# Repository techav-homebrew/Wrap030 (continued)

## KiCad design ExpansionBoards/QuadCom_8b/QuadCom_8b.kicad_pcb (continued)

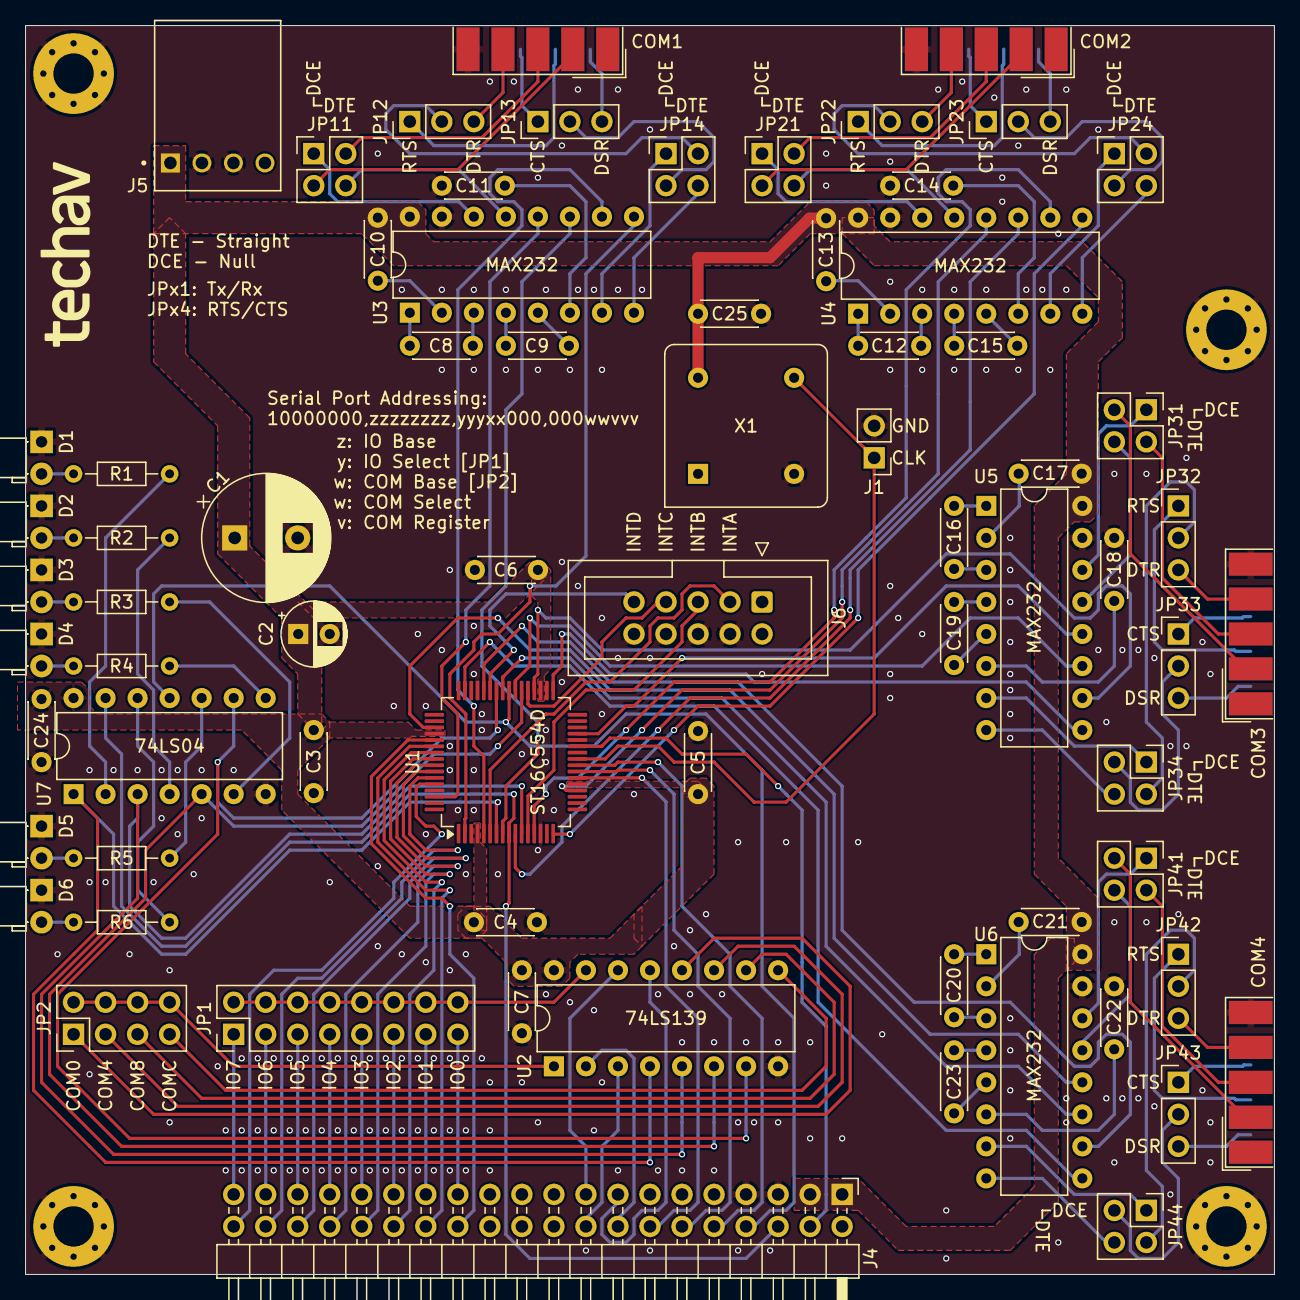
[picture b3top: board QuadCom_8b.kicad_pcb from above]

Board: 2 copper layers, 99.1 x 99.1 mm, 75 parts (0 on the bottom side), 143 nets.

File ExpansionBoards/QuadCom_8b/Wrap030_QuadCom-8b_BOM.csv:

"Reference","Value","Datasheet","Footprint","Qty","DNP","Mouser"
"C1","100uF","~","Capacitor_THT:CP_Radial_D10.0mm_P5.00mm","1","",""
"C2","10uF","~","Capacitor_THT:CP_Radial_D5.0mm_P2.50mm","1","",""
"C3,C4,C5,C6,C7,C24","100nF","~","Capacitor_THT:C_Disc_D4.3mm_W1.9mm_P5.00mm","6","",""
"C8,C9,C10,C11,C12,C13,C14,C15,C16,C17,C18,C19,C20,C21,C22,C23","1uF","~","Capacitor_THT:C_Disc_D4.3mm_W1.9mm_P5.00mm","16","",""
"COM1,COM2,COM3,COM4","DE9_Plug","~","Connector_Dsub:DSUB-9_Male_EdgeMount_P2.77mm","4","",""
"D1,D2,D3,D4,D5,D6","LED","~","LED_THT:LED_D3.0mm_Horizontal_O1.27mm_Z2.0mm","6","",""
"J4","Conn_02x20_Odd_Even","~","Connector_PinHeader_2.54mm:PinHeader_2x20_P2.54mm_Horizontal","1","",""
"J5","4-171826-4","","QuadCom_8b:TE_4-171826-4","1","",""
"J6","Conn_02x05_Odd_Even","~","Connector_IDC:IDC-Header_2x05_P2.54mm_Vertical","1","",""
"JP1","Conn_02x08_Odd_Even","~","Connector_PinHeader_2.54mm:PinHeader_2x08_P2.54mm_Vertical","1","",""
"JP2","Conn_02x04_Odd_Even","~","Connector_PinHeader_2.54mm:PinHeader_2x04_P2.54mm_Vertical","1","",""
"JP11,JP14,JP21,JP24,JP31,JP34,JP41,JP44","Conn_02x02_Odd_Even","~","Connector_PinHeader_2.54mm:PinHeader_2x02_P2.54mm_Vertical","8","",""
"JP12,JP13,JP22,JP23,JP32,JP33,JP42,JP43","Conn_01x03","~","Connector_PinHeader_2.54mm:PinHeader_1x03_P2.54mm_Vertical","8","",""
"R1,R2,R3,R4,R5,R6","4k7","~","Resistor_THT:R_Axial_DIN0204_L3.6mm_D1.6mm_P7.62mm_Horizontal","6","",""
"U1","ST16C554D","https://www.mouser.com/datasheet/2/146/ST16C554_ST16C554D_ST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","Package_QFP:LQFP-64_10x10mm_P0.5mm","1","","701-ST16C554DIQ64-F"
"U2","74LS139","http://www.ti.com/lit/ds/symlink/sn74ls139a.pdf","Package_DIP:DIP-16_W7.62mm","1","",""
"U3,U4,U5,U6","MAX232","http://www.ti.com/lit/ds/symlink/max232.pdf","Package_DIP:DIP-16_W7.62mm","4","",""
"U7","74LS04","http://www.ti.com/lit/gpn/sn74LS04","Package_DIP:DIP-14_W7.62mm","1","",""

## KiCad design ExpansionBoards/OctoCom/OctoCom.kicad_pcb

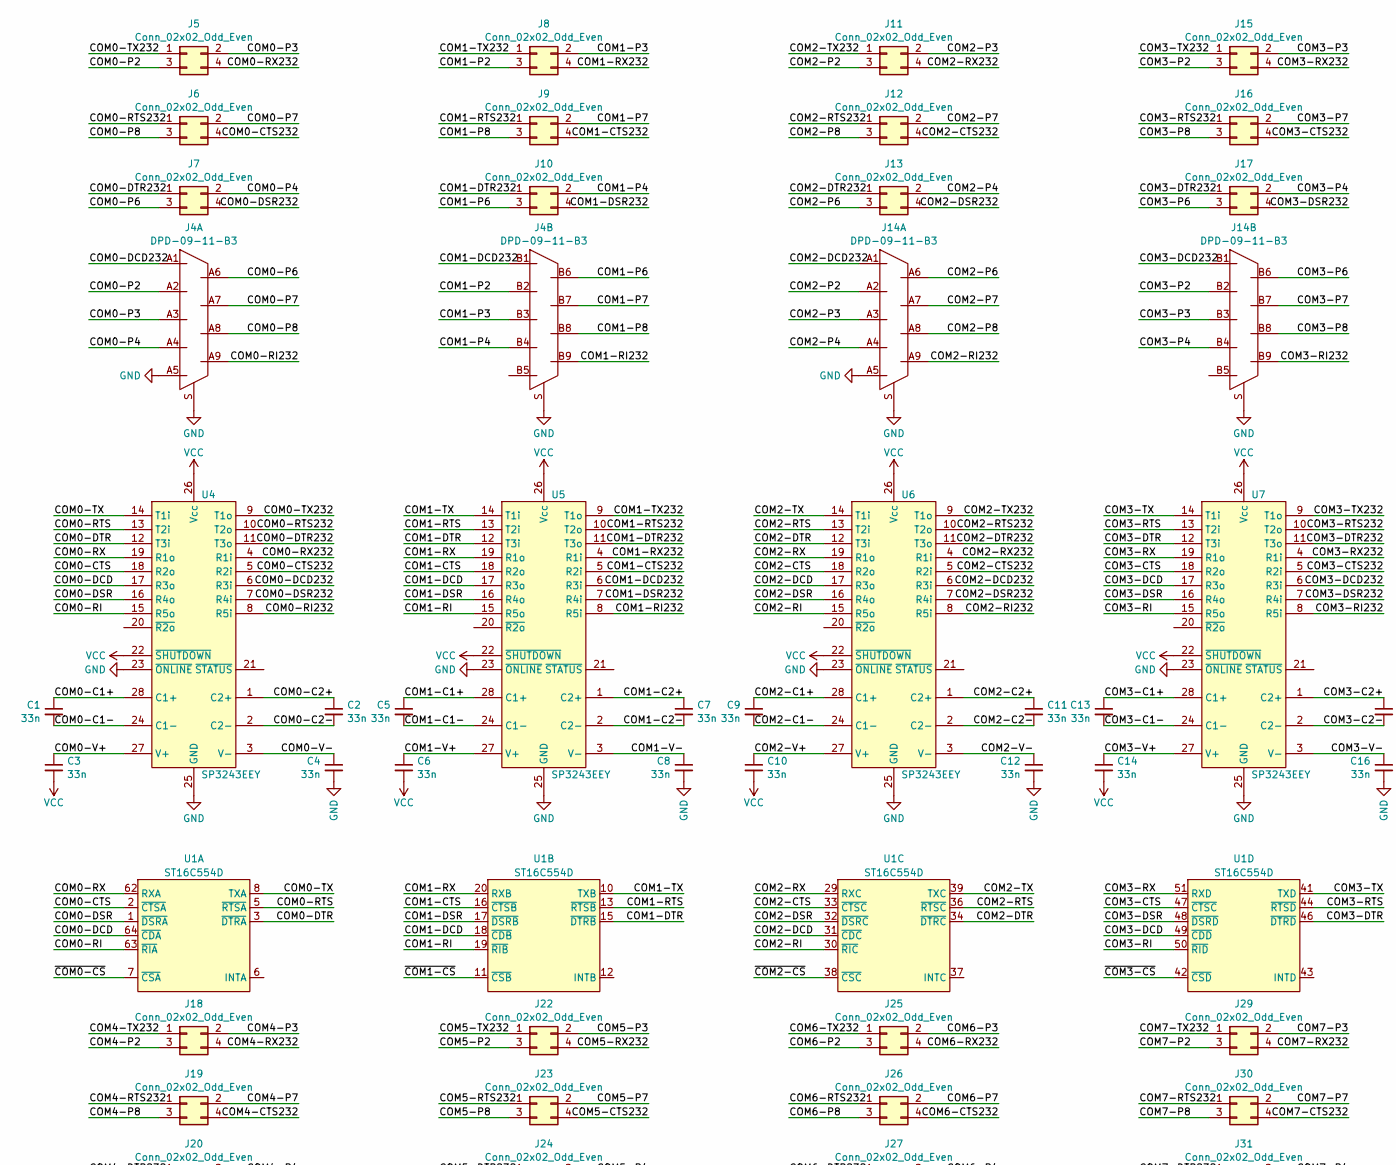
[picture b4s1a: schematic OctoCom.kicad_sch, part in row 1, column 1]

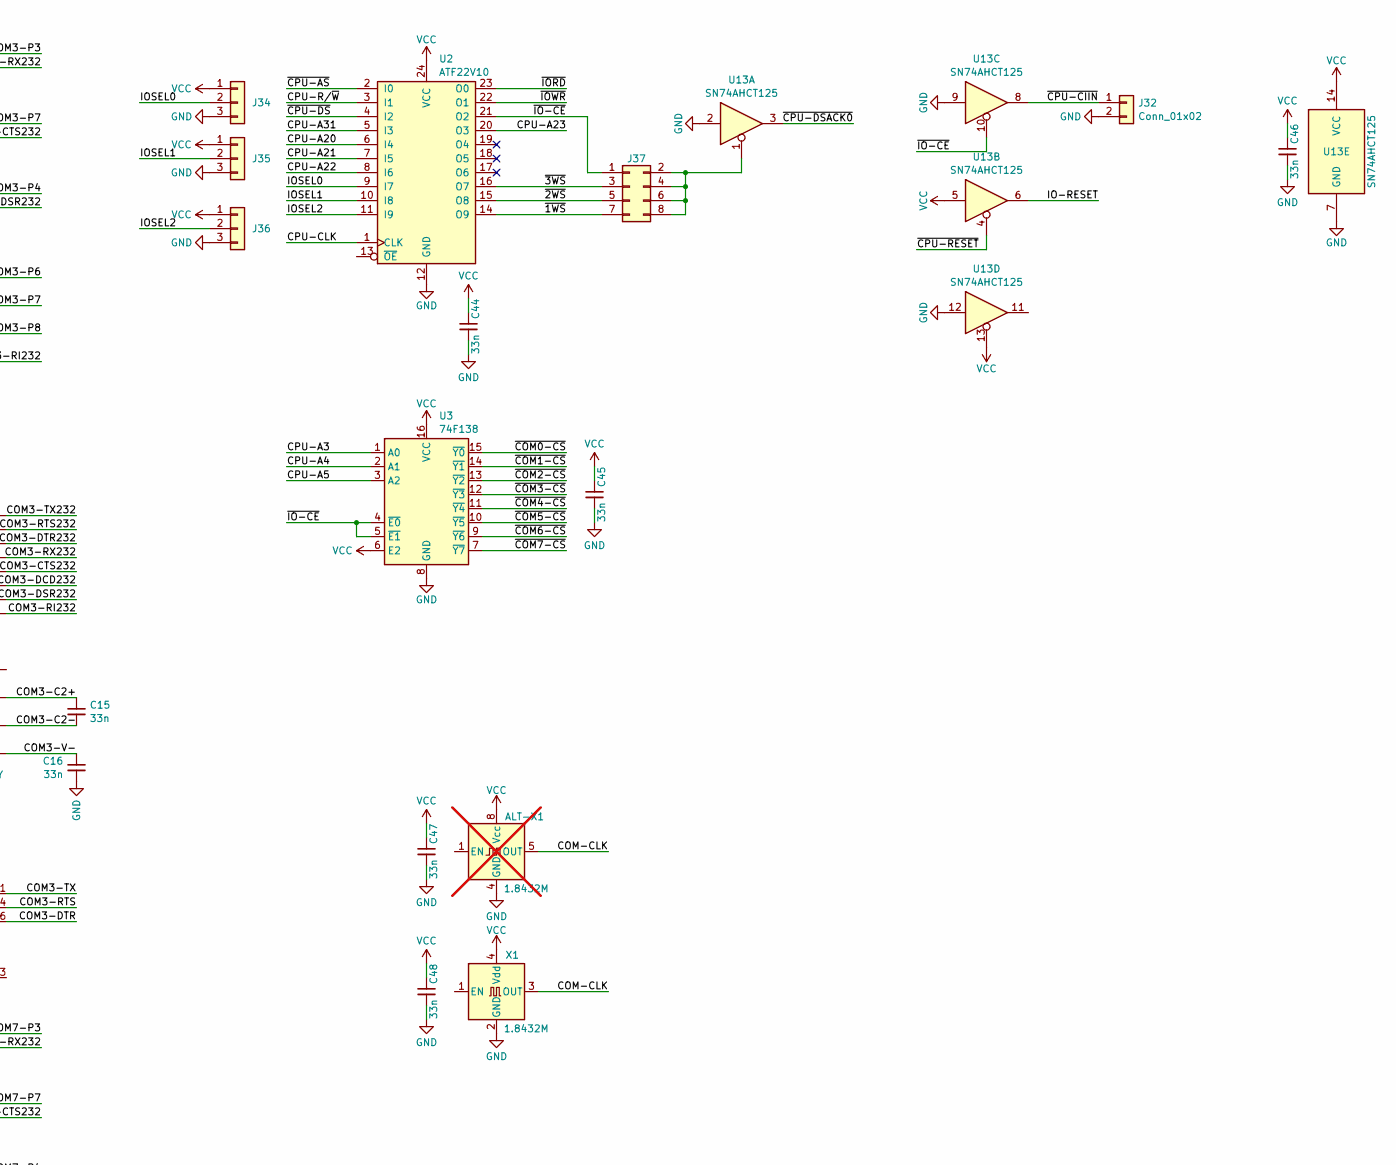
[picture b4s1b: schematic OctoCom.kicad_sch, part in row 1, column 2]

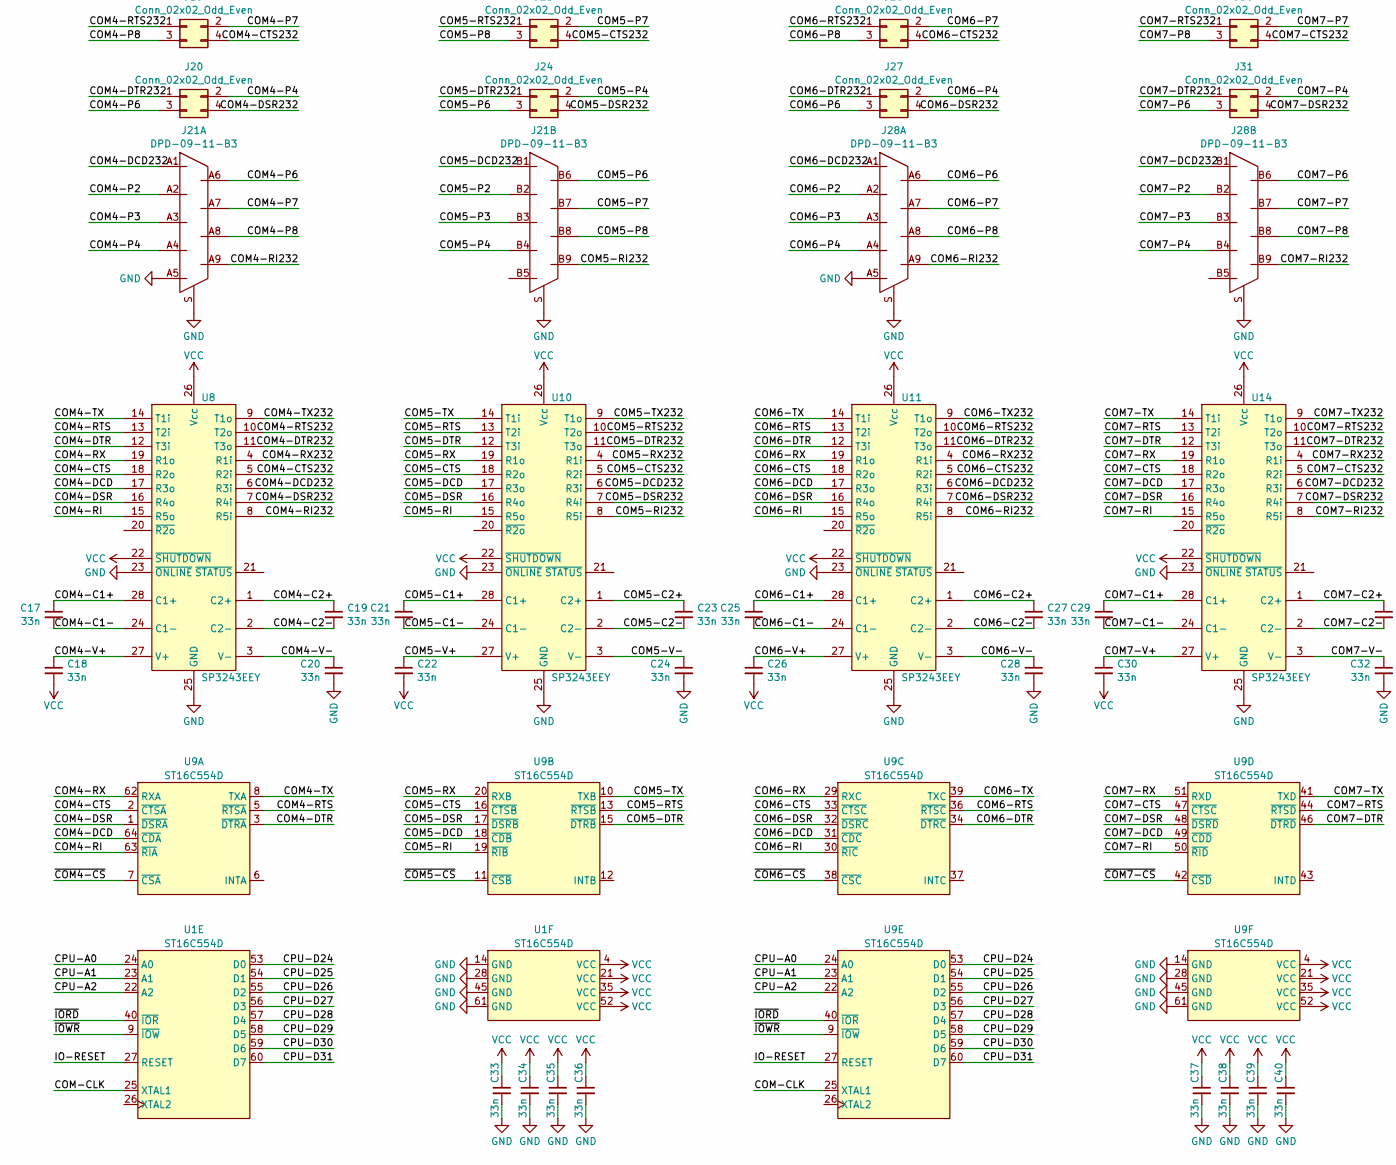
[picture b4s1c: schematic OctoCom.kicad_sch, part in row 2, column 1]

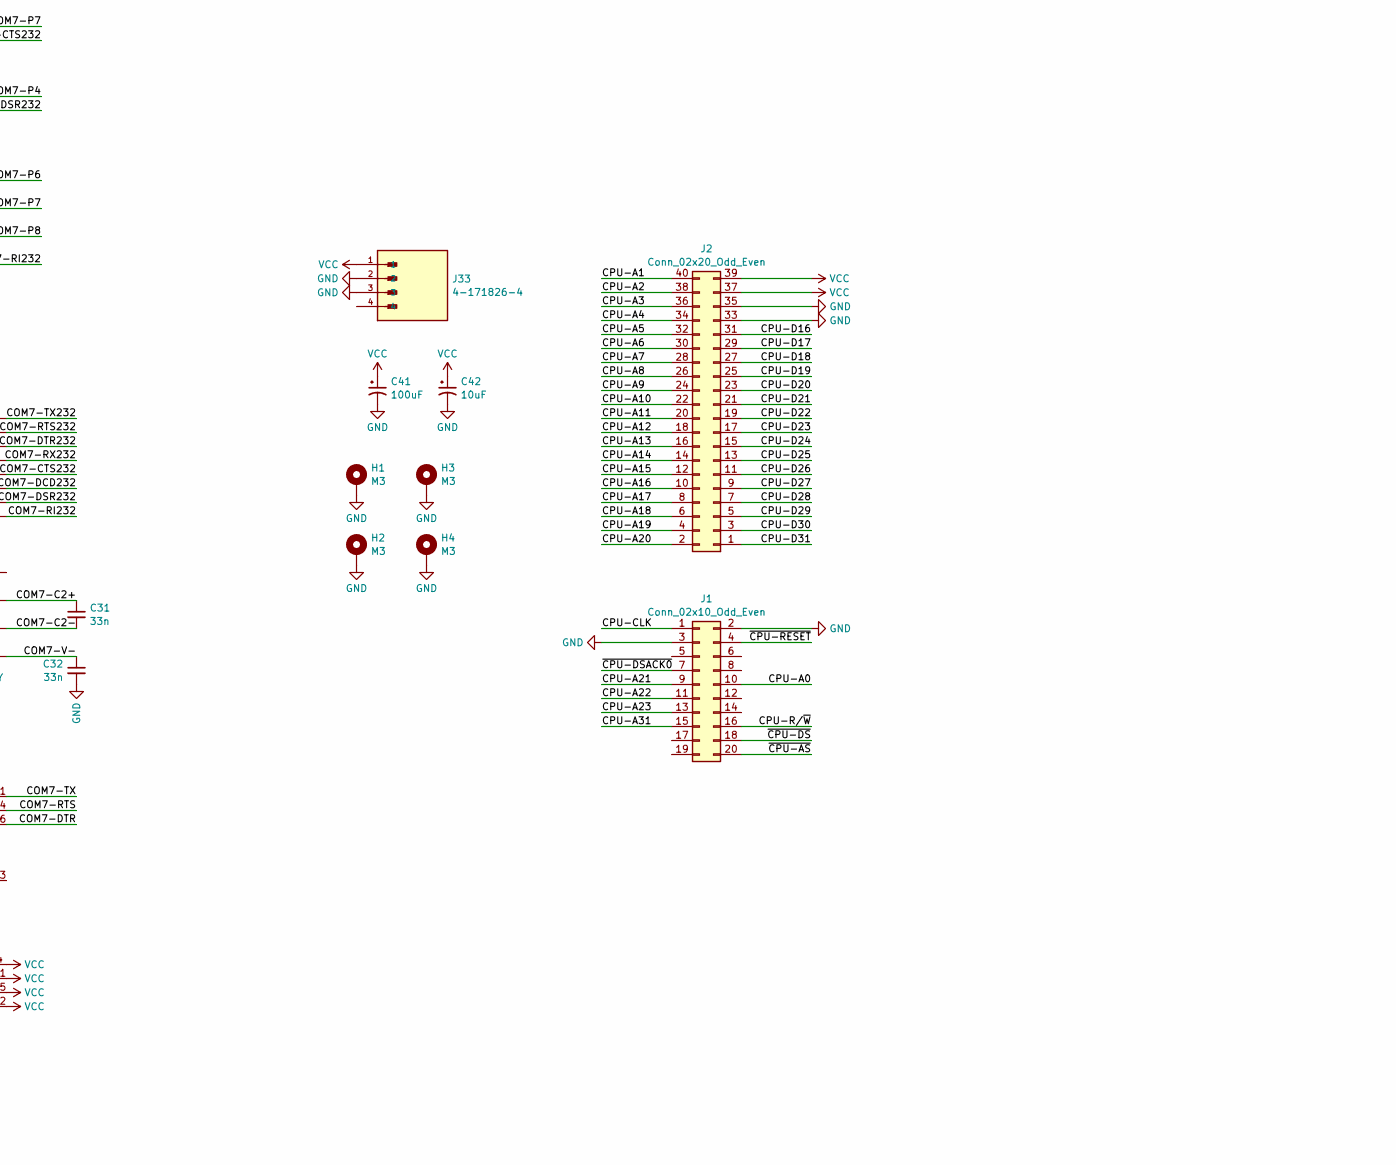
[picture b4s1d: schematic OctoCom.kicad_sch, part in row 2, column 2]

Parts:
ALT-X1: 1.8432M; Oscillator_DIP-8; Mouser 520-TCH184-X; not fitted
C1, C2, C3, C4, C5, C6, C7, C8, C9, C10, C11, C12, C13, C14, C15, C16, C17, C18, C19, C20, C21, C22, C23, C24, C25, C26, C27, C28, C29, C30, C31, C32, C33, C34, C35, C36, C37, C38, C39, C40, C44, C45, C46, C47, C48: 33n; C_0805_2012Metric_Pad1.18x1.45mm_HandSolder; Mouser 791-0805B333K160CT
C41: 100uF; CP_Radial_D10.0mm_P5.00mm
C42: 10uF; CP_Radial_D5.0mm_P2.50mm
H1, H2, H3, H4: M3; MountingHole_3.2mm_M3_Pad_Via
J1: Conn_02x10_Odd_Even; PinHeader_2x10_P2.54mm_Horizontal
J2: Conn_02x20_Odd_Even; PinHeader_2x20_P2.54mm_Horizontal
J4, J14, J21, J28: DPD-09-11-B3; Mouser 737-DPD-09-11-B3
J5, J6, J7, J8, J9, J10, J11, J12, J13, J15, J16, J17, J18, J19, J20, J22, J23, J24, J25, J26, J27, J29, J30, J31: Conn_02x02_Odd_Even; PinHeader_2x02_P2.54mm_Vertical
J32: Conn_01x02; PinHeader_1x02_P2.54mm_Vertical
J33: 4-171826-4; TE_4-171826-4
J34, J35, J36: Conn_01x03; PinHeader_1x03_P2.54mm_Vertical
J37: Conn_02x04_Odd_Even; PinHeader_2x04_P2.54mm_Vertical
U1, U9: ST16C554D; LQFP-64_10x10mm_P0.5mm; Mouser 701-ST16C554DIQ64-F
U2: ATF22V10; DIP-24_W7.62mm; Mouser 556-AF22V10C7PX
U3: 74F138; DIP-16_W7.62mm; Mouser 595-SN74F138N
U4, U5, U6, U7, U8, U10, U11, U14: SP3243EEY; TSSOP-28_4.4x9.7mm_P0.65mm; Mouser 701-SP3243EEY-L
U13: SN74AHCT125; SO-14_3.9x8.65mm_P1.27mm; Mouser 595-SN74AHCT125DR
X1: 1.8432M; Oscillator_SMD_Abracon_ASV-4Pin_7.0x5.1mm; JLC C386895

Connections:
/COM0-C1+: C1.1, U4.28 (C1+)
/COM0-C1-: C1.2, U4.24 (C1-)
/COM0-C2+: C2.1, U4.1 (C2+)
/COM0-C2-: C2.2, U4.2 (C2-)
/COM0-CTS: U1.2 (~CTSA), U4.18 (R2o)
/COM0-CTS232: J6.4, U4.5 (R2i)
/COM0-DCD: U1.64 (~CDA), U4.17 (R3o)
/COM0-DCD232: J4.A1, U4.6 (R3i)
/COM0-DSR: U1.1 (~DSRA), U4.16 (R4o)
/COM0-DSR232: J7.4, U4.7 (R4i)
/COM0-DTR: U1.3 (~DTRA), U4.12 (T3i)
/COM0-DTR232: J7.1, U4.11 (T3o)
/COM0-P2: J4.A2, J5.3
/COM0-P3: J4.A3, J5.2
/COM0-P4: J4.A4, J7.2
/COM0-P6: J4.A6, J7.3
/COM0-P7: J4.A7, J6.2
/COM0-P8: J4.A8, J6.3
/COM0-RI: U1.63 (~RIA), U4.15 (R5o)
/COM0-RI232: J4.A9, U4.8 (R5i)
/COM0-RTS: U1.5 (~RTSA), U4.13 (T2i)
/COM0-RTS232: J6.1, U4.10 (T2o)
/COM0-RX: U1.62 (RXA), U4.19 (R1o)
/COM0-RX232: J5.4, U4.4 (R1i)
/COM0-TX: U1.8 (TXA), U4.14 (T1i)
/COM0-TX232: J5.1, U4.9 (T1o)
/COM0-V+: C3.1, U4.27 (V+)
/COM0-V-: C4.1, U4.3 (V-)
/COM1-C1+: C5.1, U5.28 (C1+)
/COM1-C1-: C5.2, U5.24 (C1-)
/COM1-C2+: C7.1, U5.1 (C2+)
/COM1-C2-: C7.2, U5.2 (C2-)
/COM1-CTS: U1.16 (~CTSB), U5.18 (R2o)
/COM1-CTS232: J9.4, U5.5 (R2i)
/COM1-DCD: U1.18 (~CDB), U5.17 (R3o)
/COM1-DCD232: J4.B1, U5.6 (R3i)
/COM1-DSR: U1.17 (~DSRB), U5.16 (R4o)
/COM1-DSR232: J10.4, U5.7 (R4i)
/COM1-DTR: U1.15 (~DTRB), U5.12 (T3i)
/COM1-DTR232: J10.1, U5.11 (T3o)
/COM1-P2: J4.B2, J8.3
/COM1-P3: J4.B3, J8.2
/COM1-P4: J4.B4, J10.2
/COM1-P6: J4.B6, J10.3
/COM1-P7: J4.B7, J9.2
/COM1-P8: J4.B8, J9.3
/COM1-RI: U1.19 (~RIB), U5.15 (R5o)
/COM1-RI232: J4.B9, U5.8 (R5i)
/COM1-RTS: U1.13 (~RTSB), U5.13 (T2i)
/COM1-RTS232: J9.1, U5.10 (T2o)
/COM1-RX: U1.20 (RXB), U5.19 (R1o)
/COM1-RX232: J8.4, U5.4 (R1i)
/COM1-TX: U1.10 (TXB), U5.14 (T1i)
/COM1-TX232: J8.1, U5.9 (T1o)
/COM1-V+: C6.1, U5.27 (V+)
/COM1-V-: C8.1, U5.3 (V-)
/COM2-C1+: C9.1, U6.28 (C1+)
/COM2-C1-: C9.2, U6.24 (C1-)
/COM2-C2+: C11.1, U6.1 (C2+)
/COM2-C2-: C11.2, U6.2 (C2-)
/COM2-CTS: U1.33 (~CTSC), U6.18 (R2o)
/COM2-CTS232: J12.4, U6.5 (R2i)
/COM2-DCD: U1.31 (~CDC), U6.17 (R3o)
/COM2-DCD232: J14.A1, U6.6 (R3i)
/COM2-DSR: U1.32 (~DSRC), U6.16 (R4o)
/COM2-DSR232: J13.4, U6.7 (R4i)
/COM2-DTR: U1.34 (~DTRC), U6.12 (T3i)
/COM2-DTR232: J13.1, U6.11 (T3o)
/COM2-P2: J11.3, J14.A2
/COM2-P3: J11.2, J14.A3
/COM2-P4: J13.2, J14.A4
/COM2-P6: J13.3, J14.A6
/COM2-P7: J12.2, J14.A7
/COM2-P8: J12.3, J14.A8
/COM2-RI: U1.30 (~RIC), U6.15 (R5o)
/COM2-RI232: J14.A9, U6.8 (R5i)
/COM2-RTS: U1.36 (~RTSC), U6.13 (T2i)
/COM2-RTS232: J12.1, U6.10 (T2o)
/COM2-RX: U1.29 (RXC), U6.19 (R1o)
/COM2-RX232: J11.4, U6.4 (R1i)
/COM2-TX: U1.39 (TXC), U6.14 (T1i)
/COM2-TX232: J11.1, U6.9 (T1o)
/COM2-V+: C10.1, U6.27 (V+)
/COM2-V-: C12.1, U6.3 (V-)
/COM3-C1+: C13.1, U7.28 (C1+)
/COM3-C1-: C13.2, U7.24 (C1-)
/COM3-C2+: C15.1, U7.1 (C2+)
/COM3-C2-: C15.2, U7.2 (C2-)
/COM3-CTS: U1.47 (~CTSC), U7.18 (R2o)
/COM3-CTS232: J16.4, U7.5 (R2i)
/COM3-DCD: U1.49 (~CDD), U7.17 (R3o)
/COM3-DCD232: J14.B1, U7.6 (R3i)
/COM3-DSR: U1.48 (~DSRD), U7.16 (R4o)
/COM3-DSR232: J17.4, U7.7 (R4i)
/COM3-DTR: U1.46 (~DTRD), U7.12 (T3i)
/COM3-DTR232: J17.1, U7.11 (T3o)
/COM3-P2: J14.B2, J15.3
/COM3-P3: J14.B3, J15.2
/COM3-P4: J14.B4, J17.2
/COM3-P6: J14.B6, J17.3
/COM3-P7: J14.B7, J16.2
/COM3-P8: J14.B8, J16.3
/COM3-RI: U1.50 (~RID), U7.15 (R5o)
/COM3-RI232: J14.B9, U7.8 (R5i)
/COM3-RTS: U1.44 (~RTSD), U7.13 (T2i)
/COM3-RTS232: J16.1, U7.10 (T2o)
/COM3-RX: U1.51 (RXD), U7.19 (R1o)
/COM3-RX232: J15.4, U7.4 (R1i)
/COM3-TX: U1.41 (TXD), U7.14 (T1i)
/COM3-TX232: J15.1, U7.9 (T1o)
/COM3-V+: C14.1, U7.27 (V+)
/COM3-V-: C16.1, U7.3 (V-)
/COM4-C1+: C17.1, U8.28 (C1+)
/COM4-C1-: C17.2, U8.24 (C1-)
/COM4-C2+: C19.1, U8.1 (C2+)
/COM4-C2-: C19.2, U8.2 (C2-)
/COM4-CTS: U8.18 (R2o), U9.2 (~CTSA)
/COM4-CTS232: J19.4, U8.5 (R2i)
/COM4-DCD: U8.17 (R3o), U9.64 (~CDA)
/COM4-DCD232: J21.A1, U8.6 (R3i)
/COM4-DSR: U8.16 (R4o), U9.1 (~DSRA)
/COM4-DSR232: J20.4, U8.7 (R4i)
/COM4-DTR: U8.12 (T3i), U9.3 (~DTRA)
/COM4-DTR232: J20.1, U8.11 (T3o)
/COM4-P2: J18.3, J21.A2
/COM4-P3: J18.2, J21.A3
/COM4-P4: J20.2, J21.A4
/COM4-P6: J20.3, J21.A6
/COM4-P7: J19.2, J21.A7
/COM4-P8: J19.3, J21.A8
/COM4-RI: U8.15 (R5o), U9.63 (~RIA)
/COM4-RI232: J21.A9, U8.8 (R5i)
/COM4-RTS: U8.13 (T2i), U9.5 (~RTSA)
/COM4-RTS232: J19.1, U8.10 (T2o)
/COM4-RX: U8.19 (R1o), U9.62 (RXA)
/COM4-RX232: J18.4, U8.4 (R1i)
/COM4-TX: U8.14 (T1i), U9.8 (TXA)
/COM4-TX232: J18.1, U8.9 (T1o)
/COM4-V+: C18.1, U8.27 (V+)
/COM4-V-: C20.1, U8.3 (V-)
/COM5-C1+: C21.1, U10.28 (C1+)
/COM5-C1-: C21.2, U10.24 (C1-)
/COM5-C2+: C23.1, U10.1 (C2+)
/COM5-C2-: C23.2, U10.2 (C2-)
/COM5-CTS: U9.16 (~CTSB), U10.18 (R2o)
/COM5-CTS232: J23.4, U10.5 (R2i)
/COM5-DCD: U9.18 (~CDB), U10.17 (R3o)
/COM5-DCD232: J21.B1, U10.6 (R3i)
/COM5-DSR: U9.17 (~DSRB), U10.16 (R4o)
/COM5-DSR232: J24.4, U10.7 (R4i)
/COM5-DTR: U9.15 (~DTRB), U10.12 (T3i)
/COM5-DTR232: J24.1, U10.11 (T3o)
/COM5-P2: J21.B2, J22.3
/COM5-P3: J21.B3, J22.2
/COM5-P4: J21.B4, J24.2
/COM5-P6: J21.B6, J24.3
/COM5-P7: J21.B7, J23.2
/COM5-P8: J21.B8, J23.3
/COM5-RI: U9.19 (~RIB), U10.15 (R5o)
/COM5-RI232: J21.B9, U10.8 (R5i)
/COM5-RTS: U9.13 (~RTSB), U10.13 (T2i)
/COM5-RTS232: J23.1, U10.10 (T2o)
/COM5-RX: U9.20 (RXB), U10.19 (R1o)
/COM5-RX232: J22.4, U10.4 (R1i)
/COM5-TX: U9.10 (TXB), U10.14 (T1i)
/COM5-TX232: J22.1, U10.9 (T1o)
/COM5-V+: C22.1, U10.27 (V+)
/COM5-V-: C24.1, U10.3 (V-)
/COM6-C1+: C25.1, U11.28 (C1+)
/COM6-C1-: C25.2, U11.24 (C1-)
/COM6-C2+: C27.1, U11.1 (C2+)
/COM6-C2-: C27.2, U11.2 (C2-)
/COM6-CTS: U9.33 (~CTSC), U11.18 (R2o)
/COM6-CTS232: J26.4, U11.5 (R2i)
/COM6-DCD: U9.31 (~CDC), U11.17 (R3o)
/COM6-DCD232: J28.A1, U11.6 (R3i)
/COM6-DSR: U9.32 (~DSRC), U11.16 (R4o)
/COM6-DSR232: J27.4, U11.7 (R4i)
/COM6-DTR: U9.34 (~DTRC), U11.12 (T3i)
/COM6-DTR232: J27.1, U11.11 (T3o)
/COM6-P2: J25.3, J28.A2
/COM6-P3: J25.2, J28.A3
/COM6-P4: J27.2, J28.A4
/COM6-P6: J27.3, J28.A6
/COM6-P7: J26.2, J28.A7
/COM6-P8: J26.3, J28.A8
/COM6-RI: U9.30 (~RIC), U11.15 (R5o)
/COM6-RI232: J28.A9, U11.8 (R5i)
/COM6-RTS: U9.36 (~RTSC), U11.13 (T2i)
/COM6-RTS232: J26.1, U11.10 (T2o)
/COM6-RX: U9.29 (RXC), U11.19 (R1o)
/COM6-RX232: J25.4, U11.4 (R1i)
/COM6-TX: U9.39 (TXC), U11.14 (T1i)
/COM6-TX232: J25.1, U11.9 (T1o)
/COM6-V+: C26.1, U11.27 (V+)
/COM6-V-: C28.1, U11.3 (V-)
/COM7-C1+: C29.1, U14.28 (C1+)
/COM7-C1-: C29.2, U14.24 (C1-)
/COM7-C2+: C31.1, U14.1 (C2+)
/COM7-C2-: C31.2, U14.2 (C2-)
/COM7-CTS: U9.47 (~CTSC), U14.18 (R2o)
/COM7-CTS232: J30.4, U14.5 (R2i)
/COM7-DCD: U9.49 (~CDD), U14.17 (R3o)
/COM7-DCD232: J28.B1, U14.6 (R3i)
/COM7-DSR: U9.48 (~DSRD), U14.16 (R4o)
/COM7-DSR232: J31.4, U14.7 (R4i)
/COM7-DTR: U9.46 (~DTRD), U14.12 (T3i)
/COM7-DTR232: J31.1, U14.11 (T3o)
/COM7-P2: J28.B2, J29.3
/COM7-P3: J28.B3, J29.2
/COM7-P4: J28.B4, J31.2
/COM7-P6: J28.B6, J31.3
/COM7-P7: J28.B7, J30.2
/COM7-P8: J28.B8, J30.3
/COM7-RI: U9.50 (~RID), U14.15 (R5o)
/COM7-RI232: J28.B9, U14.8 (R5i)
/COM7-RTS: U9.44 (~RTSD), U14.13 (T2i)
/COM7-RTS232: J30.1, U14.10 (T2o)
/COM7-RX: U9.51 (RXD), U14.19 (R1o)
/COM7-RX232: J29.4, U14.4 (R1i)
/COM7-TX: U9.41 (TXD), U14.14 (T1i)
/COM7-TX232: J29.1, U14.9 (T1o)
/COM7-V+: C30.1, U14.27 (V+)
/COM7-V-: C32.1, U14.3 (V-)
/COM-CLK: ALT-X1.5 (OUT), U1.25 (XTAL1), U9.25 (XTAL1), X1.3 (OUT)
/CPU-A0: J1.10, U1.24 (A0), U9.24 (A0)
/CPU-A1: J2.40, U1.23 (A1), U9.23 (A1)
/CPU-A2: J2.38, U1.22 (A2), U9.22 (A2)
/CPU-A3: J2.36, U3.1 (A0)
/CPU-A4: J2.34, U3.2 (A1)
/CPU-A5: J2.32, U3.3 (A2)
/CPU-A6: J2.30
/CPU-A7: J2.28
/CPU-A8: J2.26
/CPU-A9: J2.24
/CPU-A10: J2.22
/CPU-A11: J2.20
/CPU-A12: J2.18
/CPU-A13: J2.16
/CPU-A14: J2.14
/CPU-A15: J2.12
/CPU-A16: J2.10
/CPU-A17: J2.8
/CPU-A18: J2.6
/CPU-A19: J2.4
/CPU-A20: J2.2, U2.6 (I4)
/CPU-A21: J1.9, U2.7 (I5)
/CPU-A22: J1.11, U2.8 (I6)
/CPU-A23: J1.13, U2.20 (O3)
/CPU-A31: J1.15, U2.5 (I3)
/CPU-CLK: J1.1, U2.1 (CLK)
/CPU-D16: J2.31
/CPU-D17: J2.29
/CPU-D18: J2.27
/CPU-D19: J2.25
/CPU-D20: J2.23
/CPU-D21: J2.21
/CPU-D22: J2.19
/CPU-D23: J2.17
/CPU-D24: J2.15, U1.53 (D0), U9.53 (D0)
/CPU-D25: J2.13, U1.54 (D1), U9.54 (D1)
/CPU-D26: J2.11, U1.55 (D2), U9.55 (D2)
/CPU-D27: J2.9, U1.56 (D3), U9.56 (D3)
/CPU-D28: J2.7, U1.57 (D4), U9.57 (D4)
/CPU-D29: J2.5, U1.58 (D5), U9.58 (D5)
/CPU-D30: J2.3, U1.59 (D6), U9.59 (D6)
/CPU-D31: J2.1, U1.60 (D7), U9.60 (D7)
/CPU-R/~W: J1.16, U2.3 (I1)
/IO-RESET: U1.27 (RESET), U9.27 (RESET), U13.6
/IOSEL0: J34.2, U2.9 (I7)
/IOSEL1: J35.2, U2.10 (I8)
/IOSEL2: J36.2, U2.11 (I9)
/~1WS: J37.7, U2.14 (O9)
/~2WS: J37.5, U2.15 (O8)
/~3WS: J37.3, U2.16 (O7)
/~COM0-CS: U1.7 (~CSA), U3.15 (~Y0)
/~COM1-CS: U1.11 (~CSB), U3.14 (~Y1)
/~COM2-CS: U1.38 (~CSC), U3.13 (~Y2)
/~COM3-CS: U1.42 (~CSD), U3.12 (~Y3)
/~COM4-CS: U3.11 (~Y4), U9.7 (~CSA)
/~COM5-CS: U3.10 (~Y5), U9.11 (~CSB)
/~COM6-CS: U3.9 (~Y6), U9.38 (~CSC)
/~COM7-CS: U3.7 (~Y7), U9.42 (~CSD)
/~CPU-AS: J1.20, U2.2 (I0)
/~CPU-CIIN: J32.1, U13.8
/~CPU-DSACK0: J1.7, U13.3
/~CPU-DS: J1.18, U2.4 (I2)
/~CPU-RESET: J1.4, U13.4
/~IO-CE: J37.1, U2.21 (O2), U3.4 (~E0), U3.5 (~E1), U13.10
/~IORD: U1.40 (~IOR), U2.23 (O0), U9.40 (~IOR)
/~IOWR: U1.9 (~IOW), U2.22 (O1), U9.9 (~IOW)
GND: ALT-X1.4 (GND), C4.2, C8.2, C12.2, C16.2, C20.2, C24.2, C28.2, C32.2, C33.2, C34.2, C35.2, C36.2, C37.2, C38.2, C39.2, C40.2, C41.2, C42.2, C44.2, C45.2, C46.2, C47.2, C48.2, H1.1, H2.1, H3.1, H4.1, J1.2, J1.3, J2.33, J2.35, J4.A5, J4.S, J14.A5, J14.S, J21.A5, J21.S, J28.A5, J28.S, J32.2, J33.2, J33.3, J34.3, J35.3, J36.3, U1.14 (GND), U1.28 (GND), U1.45 (GND), U1.61 (GND), U2.12 (GND), U3.8 (GND), U4.23 (~ONLINE), U4.25 (GND), U5.23 (~ONLINE), U5.25 (GND), U6.23 (~ONLINE), U6.25 (GND), U7.23 (~ONLINE), U7.25 (GND), U8.23 (~ONLINE), U8.25 (GND), U9.14 (GND), U9.28 (GND), U9.45 (GND), U9.61 (GND), U10.23 (~ONLINE), U10.25 (GND), U11.23 (~ONLINE), U11.25 (GND), U13.2, U13.7 (GND), U13.9, U13.12, U14.23 (~ONLINE), U14.25 (GND), X1.2 (GND)
unnamed: J37.2, J37.4, J37.6, J37.8, U13.1
VCC: ALT-X1.8 (Vcc), C3.2, C6.2, C10.2, C14.2, C18.2, C22.2, C26.2, C30.2, C33.1, C34.1, C35.1, C36.1, C37.1, C38.1, C39.1, C40.1, C41.1, C42.1, C44.1, C45.1, C46.1, C47.1, C48.1, J2.37, J2.39, J33.1, J34.1, J35.1, J36.1, U1.4 (VCC), U1.21 (VCC), U1.35 (VCC), U1.52 (VCC), U2.24 (VCC), U3.6 (E2), U3.16 (VCC), U4.22 (~SHUTDOWN), U4.26 (Vcc), U5.22 (~SHUTDOWN), U5.26 (Vcc), U6.22 (~SHUTDOWN), U6.26 (Vcc), U7.22 (~SHUTDOWN), U7.26 (Vcc), U8.22 (~SHUTDOWN), U8.26 (Vcc), U9.4 (VCC), U9.21 (VCC), U9.35 (VCC), U9.52 (VCC), U10.22 (~SHUTDOWN), U10.26 (Vcc), U11.22 (~SHUTDOWN), U11.26 (Vcc), U13.5, U13.13, U13.14 (VCC), U14.22 (~SHUTDOWN), U14.26 (Vcc), X1.4 (Vdd)

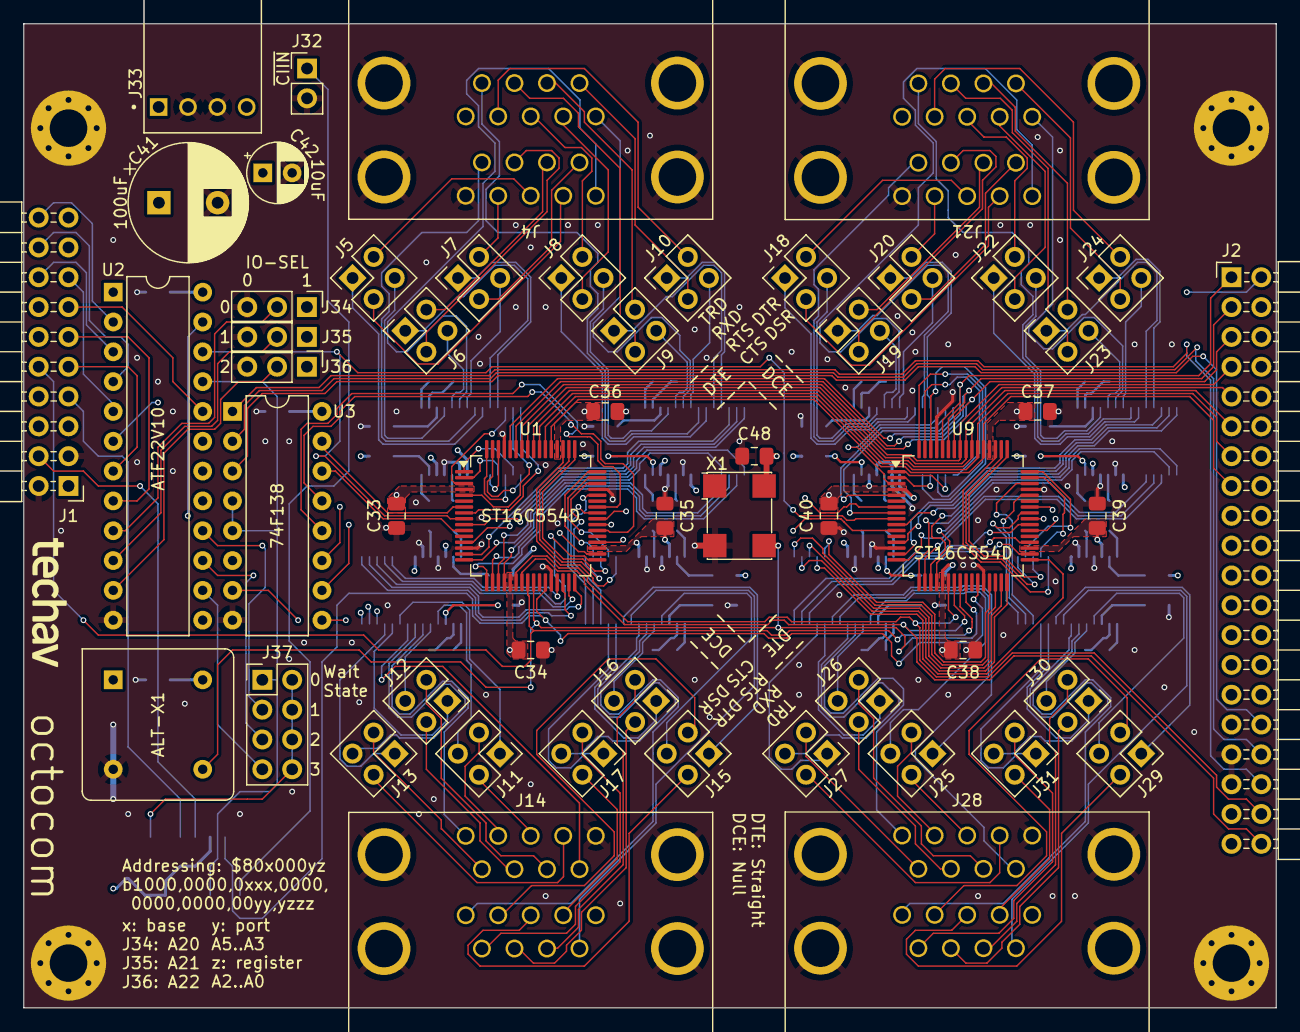
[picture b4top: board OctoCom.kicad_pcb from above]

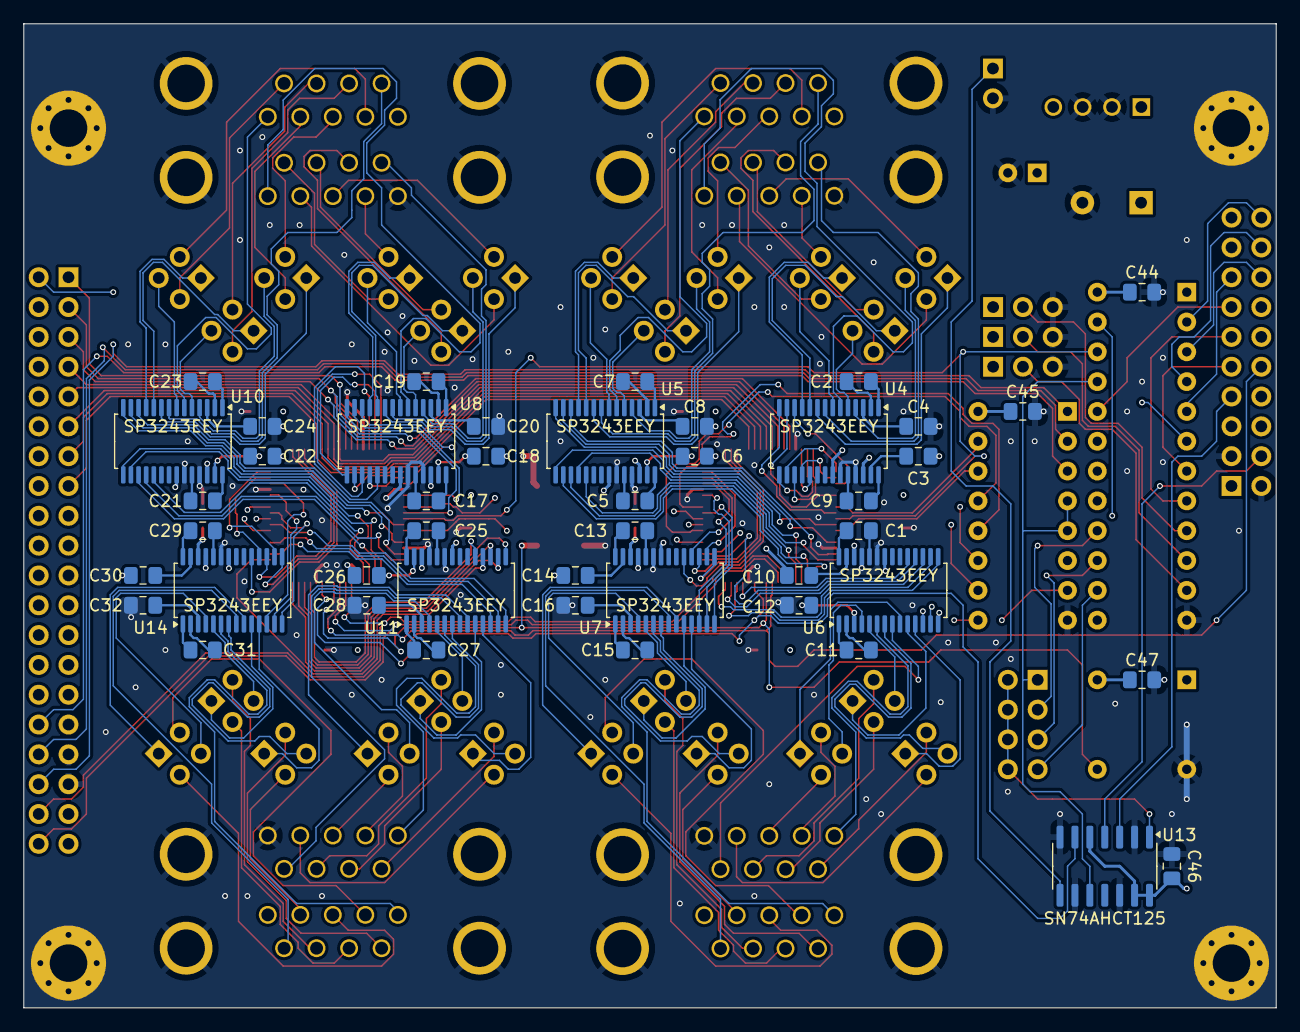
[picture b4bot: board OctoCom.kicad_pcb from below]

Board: 4 copper layers, 106.7 x 83.8 mm, 102 parts (45 on the bottom side), 272 nets.

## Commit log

2023-06-20 VCFSW 2023
2023-06-20 video logic fix
2024-04-09 Add basic IDE disk read support
2024-04-12 Add monitor commands to boot & execute from disk
2024-04-13 memCmp now returns 1 on no match to fix filename match bug
2024-04-13 clean up dead ends
2024-05-12 Assemble Mandelbrot to run from disk
2024-09-27 8b expansion boards
2024-09-27 Rough start drafting kernel for multiuser basic
2024-09-28 enable cache & draft basic loader
2024-09-28 makefile fixes
2024-09-28 correct symbols & linker script
2024-09-29 add macros, exception handling, system initialization
2024-09-29 debug startup process (it works in simulation now)
2024-10-12 debug user context save/restore
2024-10-13 user save/restore & console write working
2024-10-13 fix bug overwriting A1 with A0 on user save
2024-10-13 fix console read
2024-10-13 remove debug print statements
2025-01-04 remove remaining debug print statements
2025-01-06 Add 8-port serial expansion board
2025-01-12 rework octocom logic to use 22V10 for speed
2025-01-12 Add device selection LEDs
2025-01-13 Move from DE9 to RJ45 for serial ports
2025-01-19 Start building out supervisor console handling
2025-02-01 Multiuser Basic Kernel Updates
    - run kernel from RAM instead of ROM
    - new minimalist approach to supervisor console using only single-byte commands
2025-03-29 Archive
    This is an attempt to clean up the repository by archiving a bunch of untracked changes coming from poor branch discipline
2025-03-29 Add kicad working files to gitignore
2025-03-29 Cherry-pick from cleanup archive
2025-03-29 Cherry-pick MultiBasic Makefile from cleanup archive
2025-03-30 Multibasic missing bugfix commit
    Bugfixes for multibasic supervisor console that did not get committed before an abandoned attempt to add new features.
    (worked backwards from ghidra decompile & binary diff of ROM. compiled output of this commit matches known good ROM)
2025-03-30 Add initial support for Modem Mode
    When enabled, kernel will reset user on new connection indicated by DSR
2025-04-03 Add winCUPL outputs to gitignore
2025-04-03 Octocom fix wait state generator
    - wait state outputs should be active low
2025-04-03 Mainboard Glue - Remove video cycles
    - Remove custom video cycles used for interfacing SE-VGA card
2025-04-04 Rework Memory Map
    - Reduce ROM wait states to 3 (for 55ns ROM at 50MHz)
    - Rework memory map for contiguous 16MB RAM at address 0
    - Remove SRAM synchronous bus cycles
    - Add Function Code checking for non-CPU space cycles
    - Add interrupt autovector cycle
    - Update MultiBasic linker for new memory map
2025-04-11 Bus cycle fixes
    - assert DSACK for overlay cycles
    - assert Cache Inhibit for all cycles above 2GB boundary
    - hold STERM in high-impedance
2025-04-11 DRAM Controller
    - add initial DRAM control logic
    - add DRAM board Eagle project files
2025-04-11 Update MultiBasic bootloader for testing new DRAM
    - move reset vector to runtime ROM address instead of overlay ROM address
    - disable startup overlay prior to memory initialization
    - add print macros which don't touch RAM, to aid debugging
    - add very basic memory tests to confirm RAM is operational before continuing with boot
2025-04-11 DRAM card gerbers
    - add DRAM card gerbers that were omitted from previous DRAM controller commit
2025-04-11 Set VBR to ROM vector table before disabling overlay
2025-04-12 DRAM Control
    - hold cycle state until cpu de-asserts AS to avoid prematurely starting another DRAM cycle
    - lower refresh interval to reduce resource utilization
    - (temporary) add outputs to debug current state machine state
2025-04-13 DRAM Control
    - rework DRAM control logic to be cleaner
2025-04-13 Fix Exception Printing
    - add 4 to offsets when reading stack frame to account for pushed return address
2025-04-13 Bus error fix
    - remove bus error handling from main board glue memcycle
2025-04-13 Update Multibasic bootloader
    linker:
    - set rom size to 128k
    multibasic kernel:
    - rebuild startup load & verify routine
2025-04-13 Remove old mainboard glue logic
2025-04-19 Bootloader first draft
    First pass at a bootloader to read & execute "BOOT.BIN" from a
    FAT-formatted disk. It compiles, but is incomplete.
    Needs machine-specific implementation of low-level disk access functions
    outlined in "ff.h"
2025-04-20 Continue developing Bootloader
    - linker script put BSS at top of RAM
    - add machine-specific disk functions for ff diskio.c
    - add register printing helper functions
    - add minimal RAM data bus test to bootloader
2025-04-22 Testing Bootloader
    - add 'wdisk' directory in top-level makefile for clean
    - change startup print functions back to macros for reliabilty
    - set interrupt & supervisor stack pointers after testing RAM
    - add startup tests for assembly & C subroutine branch/return
    - add C print functions for debugging
2025-04-22 Bootloader Linker Script Fixes
    - fix ram/rom region definitions
    - mark rom code as loading from ram region so it gets burned to ROM properly (could use more cleanup..)
2025-04-23 Fix hardware pointer definitions
    They don't need to be declared as pointers at all
2025-04-23 Add .dump to Makefile clean target
2025-04-24 Debug bootloader
    - add runtime exception vector table with more detailed debugging
    - fix endian swap when writing data read from disk to memory
2025-04-24 Bootloader disable debugging
2025-04-24 Multibasic run from disk
    - makefile change output to BOOT.BIN for bootloader compatibility
    - update exception handling for better debugging
    - kernel set %msp, %isp, %vbr & initialize USERNUM on startup
2025-04-26 Add programmable timer to DRAM glue logic
    add simple test program for timer
2025-04-27 Preemptive Multibasic
    - add timer interrupt support to Multibasic kernel for pre-emptive multitasking.
2025-05-25 disable debug, increase disk ready timeout
2025-05-26 modem mode debugging
    - update user memory map to 1MB per user
    - send modem initialization string when enabling modem mode
    - bugfix for toggling modem mode from supervisor console
    - don't immediately switch to modem mode users when call starts
2025-05-27 Assert DTR/RTS on initialization
2025-05-30 Set modem quiet mode
2025-05-31 Add MMU table initialization
    Add new MMU initialization functions: (incomplete)
    - initialize supervisor table for R/W access to main memory
    - initialize user table for R/W access to user memory & RO access to BASIC
2025-06-01 Debug supervisor MMU initialization
    Supervisor MMU functional
    User MMU not functional
2025-06-01 Fix user MMU table initialization
2025-06-04 Clear cache on task switch
    Clearing cache required for stability
    Also:
    - disable MMU debug print
    - improve exception printout
    - update linker for larger exception handling code
2025-06-06 Add disk & FFS functions
    - pull in libc, libff, & wdisk from bootloader
    - update linker to add new libraries
    - update linker to allocate user disk buffers
2025-06-06 Add file open/close/read syscalls
    - add SysTrapFileOpen, SysTrapFileClose, SysTrapFileRead
    - update linker to allocate filesystem & file buffers for all users
    - add filesystem & file buffer pointers to user table
    - initialize filesystem & file buffer pointers with user init
2025-06-07 Add file read functions
    they almost work ...
2025-06-07 Don't clobber A0 in load vector
2025-06-07 Disable debug print
2025-06-08 Add disk directory print to BASIC
    currently only works with CALL $100178; does not work with DIR
2025-06-08 Add disk directory print to BASIC ("CAT")
    - add `CAT` command to BASIC
    - disable debug print
    - fix CAT table printout formatting
2025-06-08 Fix LIST table order
    LIST table must be in same order as token table
2025-06-08 Fix reset user on exception
2025-06-09 Add BASIC example programs
2025-06-14 Add FPU arithmetic functions to EhBASIC
    - add FADD, FSUB, FMUL, FDIV
    they mostly work, but something broke the built-in functions
    - lots of formatting cleanup
2025-06-15 Print space after filenames
    - fallback for terminals that don't support horizontal tab,
    make sure that at least a single space gets printed between filenames
